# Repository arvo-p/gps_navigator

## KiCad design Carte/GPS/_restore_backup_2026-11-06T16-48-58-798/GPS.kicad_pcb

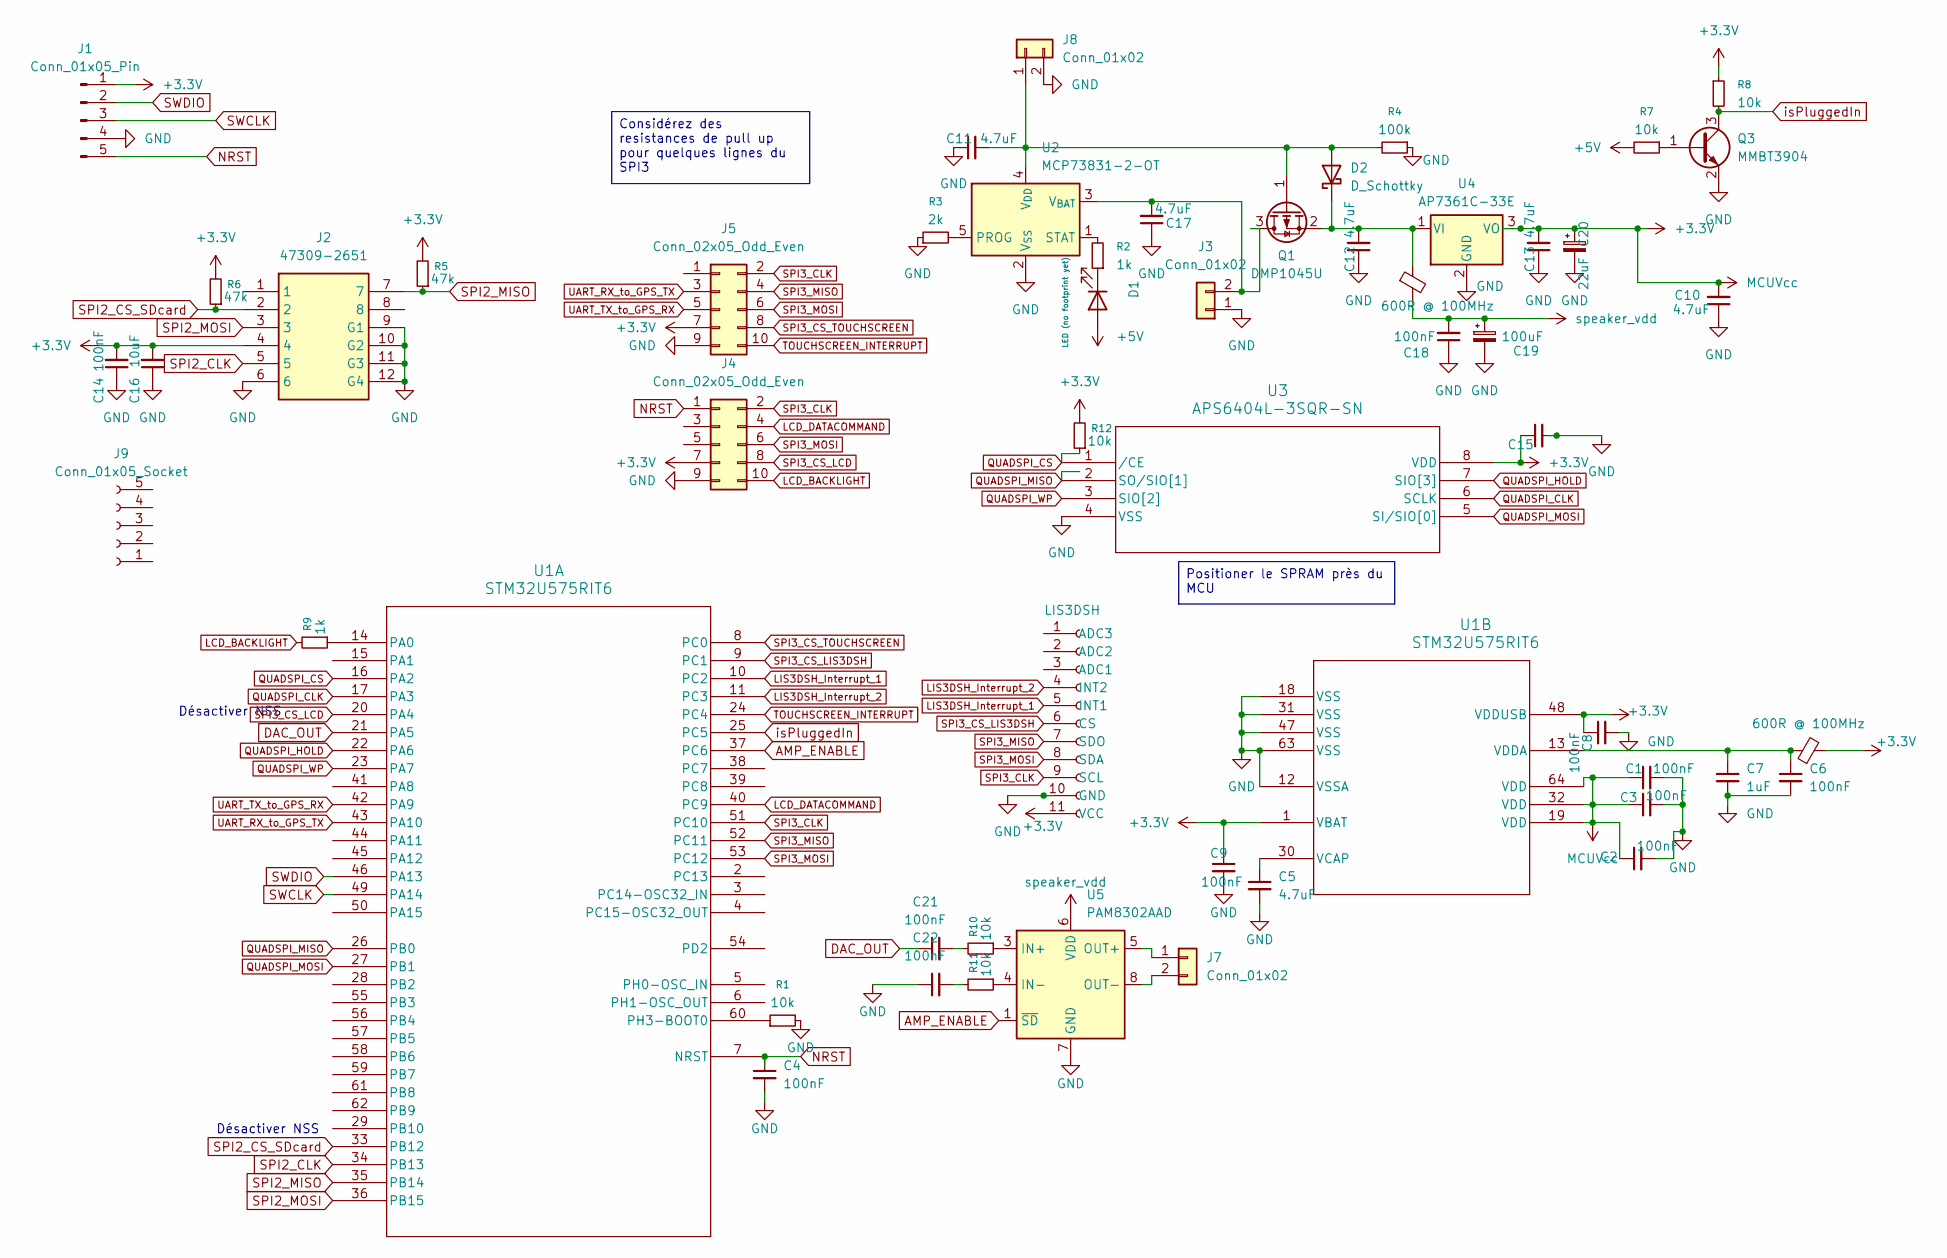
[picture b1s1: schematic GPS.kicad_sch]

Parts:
C1, C2, C3, C4, C6, C8, C9, C14, C15, C18, C21, C22: 100nF; C_0805_2012Metric
C5, C10, C11, C12, C13, C17: 4.7uF; C_0805_2012Metric
C7: 1uF; C_0805_2012Metric
C16: 10uF; C_0805_2012Metric
C19: 100uF; CP_Elec_6.3x5.4
C20: 22uF; CP_Elec_6.3x5.4
D1: LED (no footprint yet); LED_0805_2012Metric
D2: D_Schottky; D_SOD-123
FB1, FB2: 600R @ 100MHz; L_0805_2012Metric
J1: Conn_01x05_Pin; PinHeader_1x05_P2.54mm_Vertical
J2: 47309-2651; 473092651; Manufacturer_Part_Number 47309-2651; Mouser Part Number 538-47309-2651
J3, J8: Conn_01x02
J4, J5: Conn_02x05_Odd_Even; PinHeader_2x05_P2.00mm_Vertical
J6: LIS3DSH; LIS3DSH_breakout
J7: Conn_01x02; PinHeader_1x02_P2.00mm_Vertical
J9: Conn_01x05_Socket; PinHeader_1x05_P2.54mm_Vertical
Q1: DMP1045U; SOT-23-5_HandSoldering
Q3: MMBT3904; SOT-23
R1, R7, R8, R10, R11, R12: 10k; R_0805_2012Metric
R2, R9: 1k; R_0805_2012Metric
R3: 2k; R_0805_2012Metric
R4: 100k; R_0805_2012Metric
R5, R6: 47k; R_0805_2012Metric
U1: STM32U575RIT6; LQFP64-10x10mm_STM
U2: MCP73831-2-OT; SOT-23-5
U3: APS6404L-3SQR-SN; APS6404L-3SQR-SN_APY-M
U4: AP7361C-33E; SOT-223-3_TabPin2
U5: PAM8302AAD; SOIC_2AADCR_DIO-M

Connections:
+3.3V: C1.1, C2.1, C3.1, C8.1, C9.1, C10.2, C13.2, C14.2, C15.1, C16.2, C20.1, FB1.2, J1.1, J2.4, J4.7, J5.7, J6.11 (VCC), R5.2, R6.2, R8.1, R12.2, U1.1 (VBAT), U1.19 (VDD), U1.32 (VDD), U1.48 (VDDUSB), U1.64 (VDD), U3.8 (VDD), U4.3 (VO); also elsewhere on the board
+5V: D1.2 (A), R7.2
AMP_ENABLE: U1.37 (PC6), U5.1 (~SD)
DAC_OUT: C21.1, U1.21 (PA5)
GND: C1.2, C2.2, C3.2, C4.2, C5.2, C6.2, C7.2, C8.2, C9.2, C10.1, C11.1, C12.1, C13.1, C14.1, C15.2, C16.1, C17.1, C18.1, C19.2, C20.2, C22.1, J1.4, J2.6, J2.9 (G1), J2.10 (G2), J2.11 (G3), J2.12 (G4), J3.1, J4.9, J5.9, J6.10 (GND), J8.2, Q3.2 (E), R1.2, R3.1, R4.1, U1.12 (VSSA), U1.18 (VSS), U1.31 (VSS), U1.47 (VSS), U1.63 (VSS), U2.2 (V_{SS}), U3.4 (VSS), U4.2 (GND), U5.7 (GND); also elsewhere on the board
LCD_BACKLIGHT: J4.10, R9.2
LCD_DATACOMMAND: J4.4, U1.40 (PC9)
LIS3DSH_Interrupt_1: J6.5 (INT1), U1.10 (PC2)
LIS3DSH_Interrupt_2: J6.4 (INT2), U1.11 (PC3)
NRST: C4.1, J1.5, J4.1, U1.7 (NRST)
unnamed: C21.2, R10.2
unnamed: C22.2, R11.2
unnamed: D1.1 (K), R2.1
unnamed: C11.2, D2.2 (A), J8.1, Q1.1 (G), R4.2, U2.4 (V_{DD})
unnamed: C12.2, D2.1 (K), FB2.1, Q1.2 (S), U4.1 (VI)
unnamed: C17.2, J3.2, Q1.3 (D), U2.3 (V_{BAT})
unnamed: J7.1, U5.5 (OUT+)
unnamed: J7.2, U5.8 (OUT-)
unnamed: Q3.1 (B), R7.1
unnamed: R9.1, U1.14 (PA0)
unnamed: R1.1, U1.60 (PH3-BOOT0)
unnamed: C5.1, U1.30 (VCAP)
unnamed: C6.1, C7.1, FB1.1, U1.13 (VDDA)
unnamed: R3.2, U2.5 (PROG)
unnamed: R2.2, U2.1 (STAT)
unnamed: R10.1, U5.3 (IN+)
unnamed: R11.1, U5.4 (IN-)
QUADSPI_CLK: U1.17 (PA3), U3.6 (SCLK)
QUADSPI_CS: R12.1, U1.16 (PA2), U3.1 (/CE)
QUADSPI_HOLD: U1.22 (PA6), U3.7 (SIO[3])
QUADSPI_MISO: U1.26 (PB0), U3.2 (SO/SIO[1])
QUADSPI_MOSI: U1.27 (PB1), U3.5 (SI/SIO[0])
QUADSPI_WP: U1.23 (PA7), U3.3 (SIO[2])
SPI2_CLK: J2.5, U1.34 (PB13)
SPI2_CS_SDcard: J2.2, R6.1, U1.33 (PB12)
SPI2_MISO: J2.7, R5.1, U1.35 (PB14)
SPI2_MOSI: J2.3, U1.36 (PB15)
SPI3_CLK: J4.2, J5.2, J6.9 (SCL), U1.51 (PC10)
SPI3_CS_LCD: J4.8, U1.20 (PA4)
SPI3_CS_LIS3DSH: J6.6 (CS), U1.9 (PC1)
SPI3_CS_TOUCHSCREEN: J5.8, U1.8 (PC0)
SPI3_MISO: J5.4, J6.7 (SDO), U1.52 (PC11)
SPI3_MOSI: J4.6, J5.6, J6.8 (SDA), U1.53 (PC12)
SWCLK: J1.3, U1.49 (PA14)
SWDIO: J1.2, U1.46 (PA13)
TOUCHSCREEN_INTERRUPT: J5.10, U1.24 (PC4)
UART_RX_to_GPS_TX: J5.3, U1.43 (PA10)
UART_TX_to_GPS_RX: J5.5, U1.42 (PA9)
isPluggedIn: Q3.3 (C), R8.2, U1.25 (PC5)
speaker_vdd: C18.2, C19.1, FB2.2, U5.6 (VDD)

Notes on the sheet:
Désactiver NSS
Positioner le SPRAM près du MCU
Considérez des resistances de pull up pour quelques lignes du SPI3

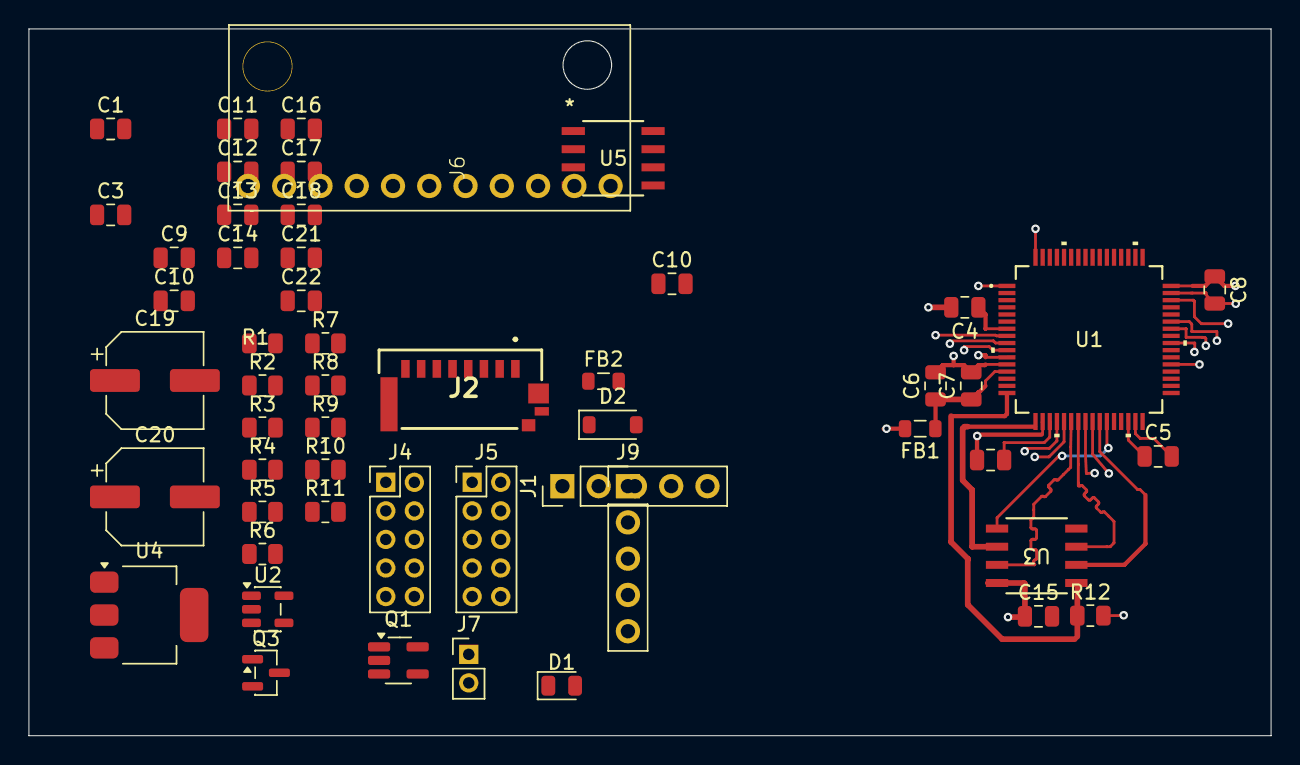
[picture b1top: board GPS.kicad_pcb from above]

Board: 4 copper layers, 87.0 x 49.5 mm, 53 parts (0 on the bottom side), 50 nets.

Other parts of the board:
C10#2: 4.7uF; C_0805_2012Metric

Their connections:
+3.3V: C10#2.2; also elsewhere on the board
GND: C10#2.1; also elsewhere on the board

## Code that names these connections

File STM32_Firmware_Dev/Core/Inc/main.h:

/**
  ******************************************************************************
  * @file    Core/Inc/main.h
  * @brief   Header for main.c module
  ******************************************************************************
  */

#ifndef __MAIN_H
#define __MAIN_H

#ifdef __cplusplus
extern "C" {
#endif

#include <stdio.h>
#include <stdint.h>
#include <stdbool.h>
#include "stm32f429i_discovery.h"
#include "stm32f429i_discovery_lcd.h"
#include "stm32f429i_discovery_sdram.h"

/*============================================================================
 * Debug Configuration
 *============================================================================*/
/* Set to 1 to show the debug HUD bar (UART status, UTC time, Fix/Satellites, Zoom),
 * or 0 to hide all debug UI overlays. */
#define APP_DEBUG_ENABLE                1

/*============================================================================
 * Hardware Port & Pin Mapping (Change here when migrating to another MCU)
 *============================================================================*/

/* --- 1. GPS UART + DMA Configuration (ATGM336H-5N) --- */
#define GPS_UART_INSTANCE               USART1
#define GPS_UART_BAUDRATE               9600U
#define GPS_UART_CLK_ENABLE()           __HAL_RCC_USART1_CLK_ENABLE()
#define GPS_UART_GET_PCLK_FREQ()        HAL_RCC_GetPCLK2Freq()
#define GPS_UART_AF                     GPIO_AF7_USART1

/* PA9 = MCU USART1_TX (connected to GPS RX) */
#define GPS_UART_TX_GPIO_PORT           GPIOA
#define GPS_UART_TX_PIN                 GPIO_PIN_9
#define GPS_UART_TX_GPIO_CLK_ENABLE()   __HAL_RCC_GPIOA_CLK_ENABLE()

/* PA10 = MCU USART1_RX (connected to GPS TX) */
#define GPS_UART_RX_GPIO_PORT           GPIOA
#define GPS_UART_RX_PIN                 GPIO_PIN_10
#define GPS_UART_RX_GPIO_CLK_ENABLE()   __HAL_RCC_GPIOA_CLK_ENABLE()

/* GPS UART Interrupt & Circular RX DMA Stream */
#define GPS_UART_IRQn                   USART1_IRQn
#define GPS_UART_IRQHandler             USART1_IRQHandler

#define GPS_DMA_CLK_ENABLE()            __HAL_RCC_DMA2_CLK_ENABLE()
#define GPS_DMA_RX_STREAM               DMA2_Stream2
#define GPS_DMA_RX_CHANNEL              4UL
#define GPS_DMA_RX_IRQn                 DMA2_Stream2_IRQn
#define GPS_DMA_RX_IRQHandler           DMA2_Stream2_IRQHandler
#define GPS_DMA_RX_ISR_REG              (DMA2->LISR)
#define GPS_DMA_RX_IFCR_REG             (DMA2->LIFCR)
#define GPS_DMA_RX_ISR_FLAGS            (DMA_LISR_HTIF2 | DMA_LISR_TCIF2 | DMA_LISR_TEIF2 | DMA_LISR_DMEIF2 | DMA_LISR_FEIF2)
#define GPS_DMA_RX_CLEAR_FLAGS          (DMA_LIFCR_CTCIF2 | DMA_LIFCR_CHTIF2 | DMA_LIFCR_CTEIF2 | DMA_LIFCR_CDMEIF2 | DMA_LIFCR_CFEIF2)

/* --- 2. microSD SPI Configuration (FatFs DiskIO) --- */
#define SD_SPI_INSTANCE                 SPI5
#define SD_SPI_CLK_ENABLE()             __HAL_RCC_SPI5_CLK_ENABLE()
#define SD_SPI_GPIO_PORT                GPIOF
#define SD_SPI_GPIO_CLK_ENABLE()        __HAL_RCC_GPIOF_CLK_ENABLE()
#define SD_SPI_SCK_PIN                  GPIO_PIN_7
#define SD_SPI_MISO_PIN                 GPIO_PIN_8
#define SD_SPI_MOSI_PIN                 GPIO_PIN_9
#define SD_SPI_AF                       GPIO_AF5_SPI5
#define SD_SPI_SLOW_PRESCALER           SPI_BAUDRATEPRESCALER_256
#define SD_SPI_FAST_PRESCALER           SPI_BAUDRATEPRESCALER_8

/* SD Card Chip Select (PC2) */
#define SD_CS_GPIO_PORT                 GPIOC
#define SD_CS_PIN                       GPIO_PIN_2
#define SD_CS_GPIO_CLK_ENABLE()         __HAL_RCC_GPIOC_CLK_ENABLE()

/* Shared SPI5 Bus Companion Pins on STM32F429I-Discovery:
 *   - Onboard L3GD20 Gyro CS (PC1) held HIGH so it never drives MISO
 *   - Onboard ILI9341 WRX/DCX (PD13) held HIGH so LCD ignores SD SPI traffic */
#define SD_GYRO_CS_GPIO_PORT            GYRO_CS_GPIO_PORT
#define SD_GYRO_CS_PIN                  GYRO_CS_PIN
#define SD_GYRO_CS_GPIO_CLK_ENABLE()    GYRO_CS_GPIO_CLK_ENABLE()

#define SD_LCD_DCX_GPIO_PORT            LCD_WRX_GPIO_PORT
#define SD_LCD_DCX_PIN                  LCD_WRX_PIN
#define SD_LCD_DCX_GPIO_CLK_ENABLE()    LCD_WRX_GPIO_CLK_ENABLE()

/* --- 3. Display, DMA2D & Board I/O Configuration --- */
#define DISP_HOR_RES                    240
#define DISP_VER_RES                    320
#define DISP_FRAME_BUFFER_ADDR          LCD_FRAME_BUFFER
#define DISP_DMA2D_INSTANCE             DMA2D

#define BOARD_LED_GREEN                 LED3
#define BOARD_LED_RED                   LED4
#define BOARD_USER_BUTTON_PIN           KEY_BUTTON_PIN

/* ATGM336H-5N (CASIC) Constellation Modes ($PCAS04) */
#define ATGM336H_MODE_GPS_ONLY          1U  /* $PCAS04,1*18 */
#define ATGM336H_MODE_BDS_ONLY          2U  /* $PCAS04,2*1B */
#define ATGM336H_MODE_GPS_BDS           3U  /* $PCAS04,3*1A */
#define ATGM336H_MODE_GLONASS_ONLY      4U  /* $PCAS04,4*1D */
#define ATGM336H_MODE_GPS_GLONASS       5U  /* $PCAS04,5*1C */
#define ATGM336H_MODE_GPS_BDS_GLONASS   7U  /* $PCAS04,7*1E */

void Toggle_Leds(void);
void App_Run(void);
void LVGL_Example_Run(void);

/* ATGM336H-5N Control API */
void GPS_ATGM336H_SetConstellation(uint8_t mode);
void GPS_ATGM336H_EnterSleep(uint16_t standby_sec);
void GPS_ATGM336H_Wakeup(void);

#ifdef __cplusplus
}
#endif

#endif /* __MAIN_H */
